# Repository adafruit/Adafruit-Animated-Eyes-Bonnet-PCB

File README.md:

## Adafruit Animated Eyes Bonnet PCB

<a href="http://www.adafruit.com/products/3356"><br/>
Click here to purchase one from the Adafruit shop</a>

PCB files for the Adafruit Animated Eyes Bonnet. Format is EagleCAD schematic and board layout
* http://www.adafruit.com/product/3356

### Description

The Snake Eyes Bonnet is a Raspberry Pi accessory for driving two 128x128 pixel OLED or TFT LCD displays, and also provides four analog inputs for sensors. It's perfect for making cosplay masks, props, spooky sculptures for halloween, animatronics, robots...anything where you want to add a pair of animated eyes!

This product is just the Pi Bonnet itself, and some headers so you can plug it into a Pi. While it will work with any Raspberry Pi with a 2x20 Header (Pi B+, Pi 2, Pi 3, Pi Zero, etc) you'll get best performance from a Pi 3 since we do some heavy duty OpenGL rendering!

**This product doesn't include two displays or connector cables!**

### License

Adafruit invests time and resources providing this open source design, please support Adafruit and open-source hardware by purchasing products from [Adafruit](https://www.adafruit.com)!

Designed by Limor Fried/Ladyada for Adafruit Industries.

Creative Commons Attribution/Share-Alike, all text above must be included in any redistribution. See license.txt for additional details.

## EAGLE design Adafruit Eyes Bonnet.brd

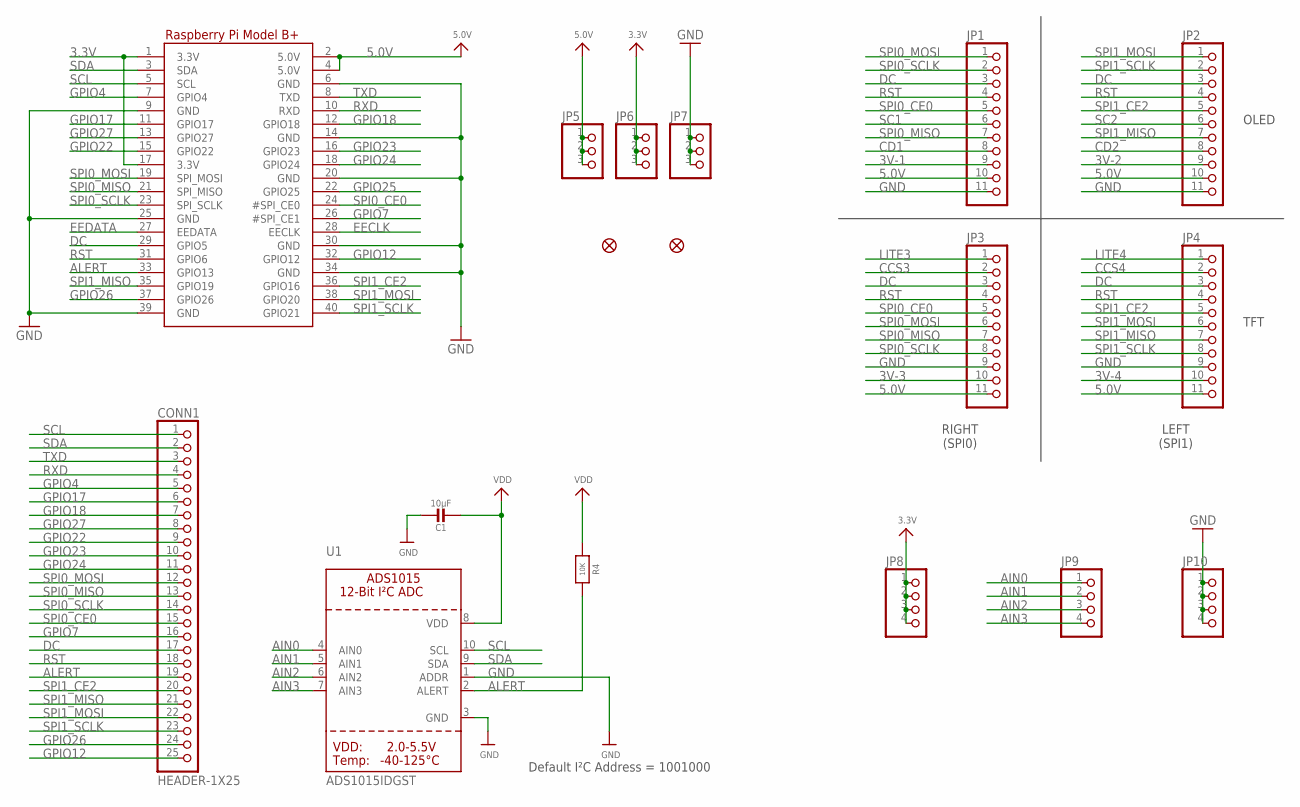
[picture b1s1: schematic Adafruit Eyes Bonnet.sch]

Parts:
C1: 10µF; 0805-NO
CONN1: HEADER-1X25; 1X25_ROUND_70MIL
FID1, FID2: FIDUCIAL""; FIDUCIAL_1MM
JP1, JP2, JP3, JP4: HEADER-1X11; 1X11_ROUND
JP5, JP6, JP7: HEADER-1X376MIL; 1X03_ROUND_76
JP8, JP9, JP10: HEADER-1X4ROUND; 1X04_ROUND
R4: 10K; 0805-NO
RPI1: RASPBERRYPI_BPLUS_PHAT; PI_BONNET
U1: ADS1015IDGST; MSOP10

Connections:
3.3V: C1.2, JP6.1, JP6.2, JP6.3, JP8.1, JP8.2, JP8.3, JP8.4, R4.1, RPI1.1 (3.3V), RPI1.17 (3.3V), U1.8 (VDD)
3V-1: JP1.9
3V-2: JP2.9
3V-3: JP3.10
3V-4: JP4.10
5.0V: JP1.10, JP2.10, JP3.11, JP4.11, JP5.1, JP5.2, JP5.3, RPI1.2 (5.0V), RPI1.4 (5.0V)
AIN0: JP9.1, U1.4 (AIN0)
AIN1: JP9.2, U1.5 (AIN1)
AIN2: JP9.3, U1.6 (AIN2)
AIN3: JP9.4, U1.7 (AIN3)
ALERT: CONN1.19, R4.2, RPI1.33 (GPIO13), U1.2 (ALERT)
CCS3: JP3.2
CCS4: JP4.2
CD1: JP1.8
CD2: JP2.8
DC: CONN1.17, JP1.3, JP2.3, JP3.3, JP4.3, RPI1.29 (GPIO5)
EECLK: RPI1.28 (EECLK)
EEDATA: RPI1.27 (EEDATA)
GND: C1.1, JP1.11, JP2.11, JP3.9, JP4.9, JP7.1, JP7.2, JP7.3, JP10.1, JP10.2, JP10.3, JP10.4, RPI1.6 (GND), RPI1.9 (GND), RPI1.14 (GND), RPI1.20 (GND), RPI1.25 (GND), RPI1.30 (GND), RPI1.34 (GND), RPI1.39 (GND), U1.1 (ADDR), U1.3 (GND)
GPIO4: CONN1.5, RPI1.7 (GPIO4)
GPIO7: CONN1.16, RPI1.26 (#SPI_CE1)
GPIO12: CONN1.25, RPI1.32 (GPIO12)
GPIO17: CONN1.6, RPI1.11 (GPIO17)
GPIO18: CONN1.7, RPI1.12 (GPIO18)
GPIO22: CONN1.9, RPI1.15 (GPIO22)
GPIO23: CONN1.10, RPI1.16 (GPIO23)
GPIO24: CONN1.11, RPI1.18 (GPIO24)
GPIO25: RPI1.22 (GPIO25)
GPIO26: CONN1.24, RPI1.37 (GPIO26)
GPIO27: CONN1.8, RPI1.13 (GPIO27)
LITE3: JP3.1
LITE4: JP4.1
RST: CONN1.18, JP1.4, JP2.4, JP3.4, JP4.4, RPI1.31 (GPIO6)
RXD: CONN1.4, RPI1.10 (RXD)
SC1: JP1.6
SC2: JP2.6
SCL: CONN1.1, RPI1.5 (SCL), U1.10 (SCL)
SDA: CONN1.2, RPI1.3 (SDA), U1.9 (SDA)
SPI0_CE0: CONN1.15, JP1.5, JP3.5, RPI1.24 (#SPI_CE0)
SPI0_MISO: CONN1.13, JP1.7, JP3.7, RPI1.21 (SPI_MISO)
SPI0_MOSI: CONN1.12, JP1.1, JP3.6, RPI1.19 (SPI_MOSI)
SPI0_SCLK: CONN1.14, JP1.2, JP3.8, RPI1.23 (SPI_SCLK)
SPI1_CE2: CONN1.20, JP2.5, JP4.5, RPI1.36 (GPIO16)
SPI1_MISO: CONN1.21, JP2.7, JP4.7, RPI1.35 (GPIO19)
SPI1_MOSI: CONN1.22, JP2.1, JP4.6, RPI1.38 (GPIO20)
SPI1_SCLK: CONN1.23, JP2.2, JP4.8, RPI1.40 (GPIO21)
TXD: CONN1.3, RPI1.8 (TXD)

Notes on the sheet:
OLED
TFT
RIGHT (SPI0)
LEFT (SPI1)
Default I²C Address = 1001000

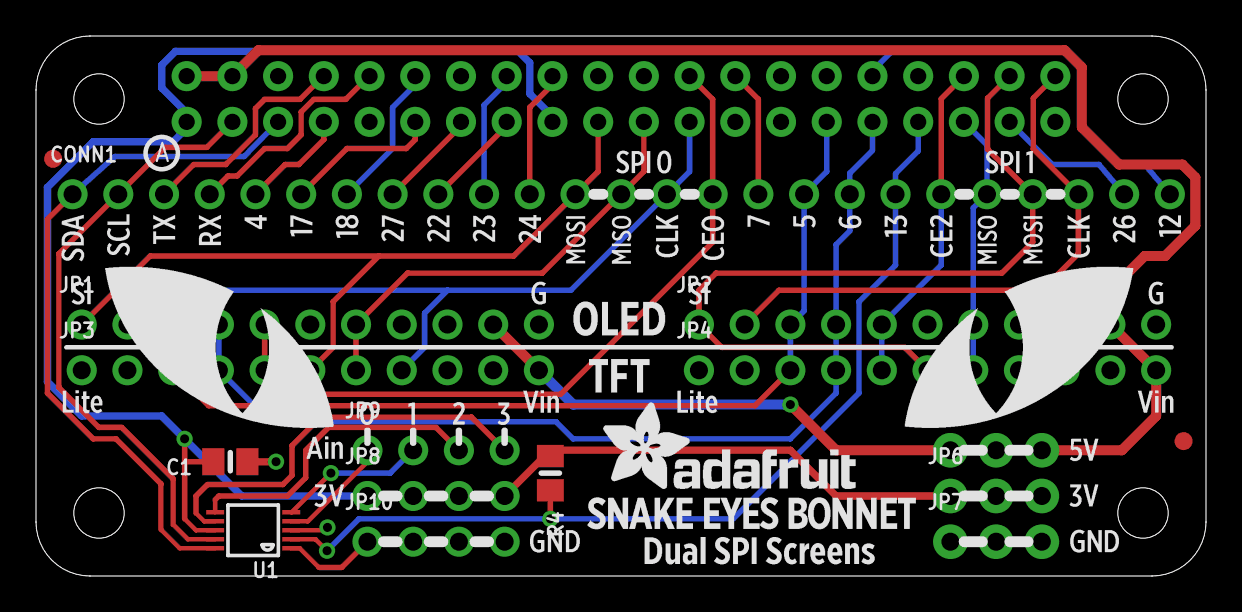
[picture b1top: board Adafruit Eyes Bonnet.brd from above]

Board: 2 copper layers, 65.0 x 30.0 mm, 18 parts (0 on the bottom side), 32 nets.

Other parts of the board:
U$8: BONNET_EYES_REVA

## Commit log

2017-01-11 init

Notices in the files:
parts and their libraries:
microbuilder: This work is placed in the public domain, and may be freely used for commercial and non-commercial work with the following conditions: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
